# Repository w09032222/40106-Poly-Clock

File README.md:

# 40106-Poly-Clock

A poly-clock module with inverted output and a swtich to choose between 3 sync modes.

mode 1:sync mode.
In this mode, two clocks will be run in the same speed but in different division.

mode 2:split mode.
In this mode, two clocks will not sync with each other.

mode 3:off-beat mode.
In this mode, clock2 will only start running when the clock1's signal is low (both of the clock are in 50% duty cycle).

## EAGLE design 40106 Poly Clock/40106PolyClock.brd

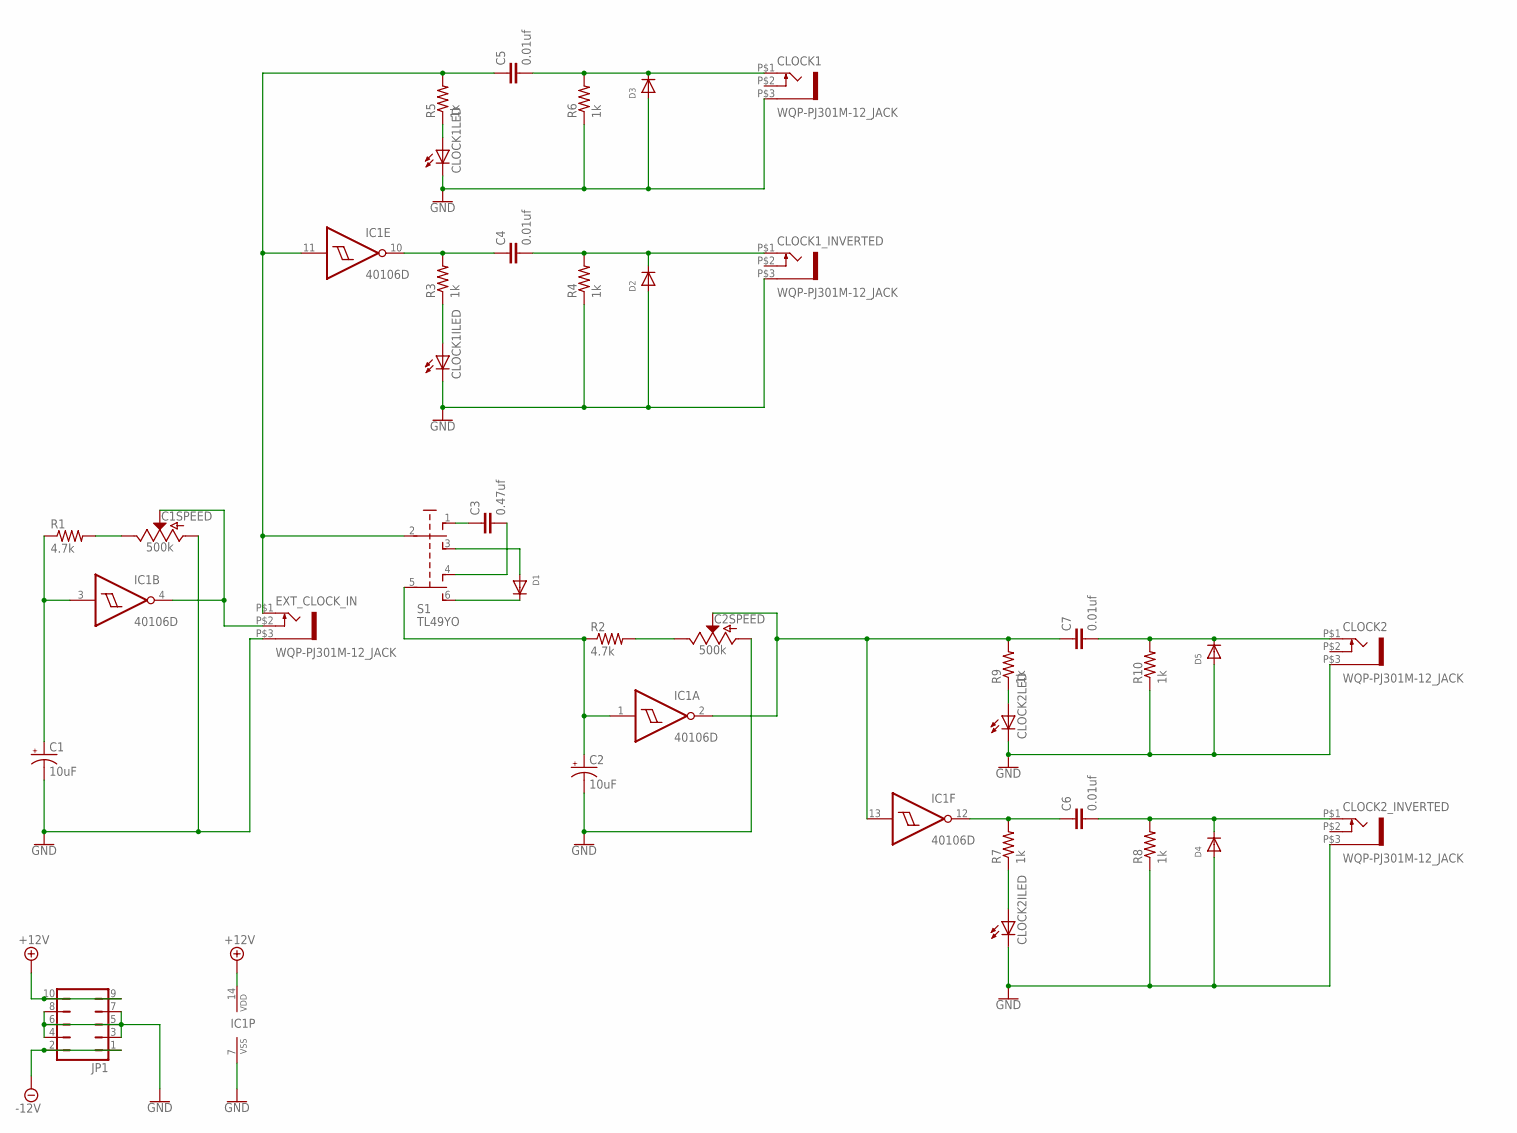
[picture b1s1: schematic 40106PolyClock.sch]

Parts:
C1, C2: 10uF; 0603-POLAR
C1SPEED, C2SPEED: 500k; POT-PTH-ALPS-KIT
C3: 0.47uf; C1206
C4, C5, C6, C7: 0.01uf; C1206
CLOCK1, CLOCK1_INVERTED, CLOCK2, CLOCK2_INVERTED: WQP-PJ301M-12_JACK
CLOCK1ILED, CLOCK1LED, CLOCK2ILED, CLOCK2LED: LED5MM
D1, D2, D3, D4, D5: DIODESOD-123; SOD-123
EXT_CLOCK_IN: WQP-PJ301M-12_JACK
IC1: 40106D; SO14
JP1: JP5Q
R1, R2: 4.7k; R1206
R3, R4, R5, R6, R7, R8, R9, R10: 1k; R1206
S1: TL49YO; TL4XYO

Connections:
+12V: IC1.14 (VDD), JP1.9, JP1.10
-12V: JP1.1, JP1.2
GND: C1.-, C1SPEED.P$3 (A), C2.-, C2SPEED.P$3 (A), CLOCK1.P$3 (1), CLOCK1ILED.K (C), CLOCK1LED.K (C), CLOCK1_INVERTED.P$3 (1), CLOCK2.P$3 (1), CLOCK2ILED.K (C), CLOCK2LED.K (C), CLOCK2_INVERTED.P$3 (1), D2.A, D3.A, D4.A, D5.A, EXT_CLOCK_IN.P$3 (1), IC1.7 (VSS), JP1.3, JP1.4, JP1.5, JP1.6, JP1.7, JP1.8, R4.1, R6.1, R8.1, R10.1
unnamed: C1.+, IC1.3 (I), R1.1
unnamed: C1SPEED.P$1 (E), R1.2
unnamed: C1SPEED.P$2 (S), EXT_CLOCK_IN.P$2 (3), IC1.4 (O)
unnamed: C5.1, EXT_CLOCK_IN.P$1 (2), IC1.11 (I), R5.2, S1.2
unnamed: C3.1, S1.1 (O)
unnamed: C3.2, S1.4 (O1)
unnamed: D1.A, S1.3 (S)
unnamed: D1.C, S1.6 (S1)
unnamed: C2.+, IC1.1 (I), R2.1, S1.5 (P1)
unnamed: C2SPEED.P$1 (E), R2.2
unnamed: C6.1, IC1.12 (O), R7.2
unnamed: CLOCK2ILED.A, R7.1
unnamed: C6.2, CLOCK2_INVERTED.P$1 (2), D4.C, R8.2
unnamed: C7.2, CLOCK2.P$1 (2), D5.C, R10.2
unnamed: C4.1, IC1.10 (O), R3.2
unnamed: CLOCK1ILED.A, R3.1
unnamed: C4.2, CLOCK1_INVERTED.P$1 (2), D2.C, R4.2
unnamed: CLOCK1LED.A, R5.1
unnamed: C5.2, CLOCK1.P$1 (2), D3.C, R6.2
unnamed: C2SPEED.P$2 (S), C7.1, IC1.2 (O), IC1.13 (I), R9.2
unnamed: CLOCK2LED.A, R9.1

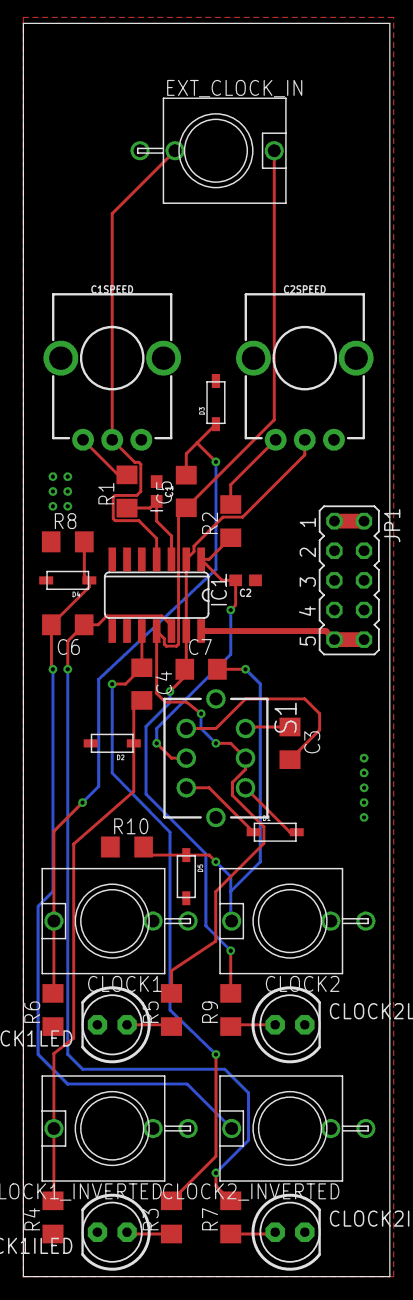
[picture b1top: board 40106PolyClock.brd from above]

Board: 2 copper layers, 31.4 x 107.4 mm, 36 parts (0 on the bottom side), 24 nets.

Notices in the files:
parts and their libraries:
SparkFun-Capacitors: Licensing: Creative Commons ShareAlike 4.0 International - https://creativecommons.org/licenses/by-sa/4.0
